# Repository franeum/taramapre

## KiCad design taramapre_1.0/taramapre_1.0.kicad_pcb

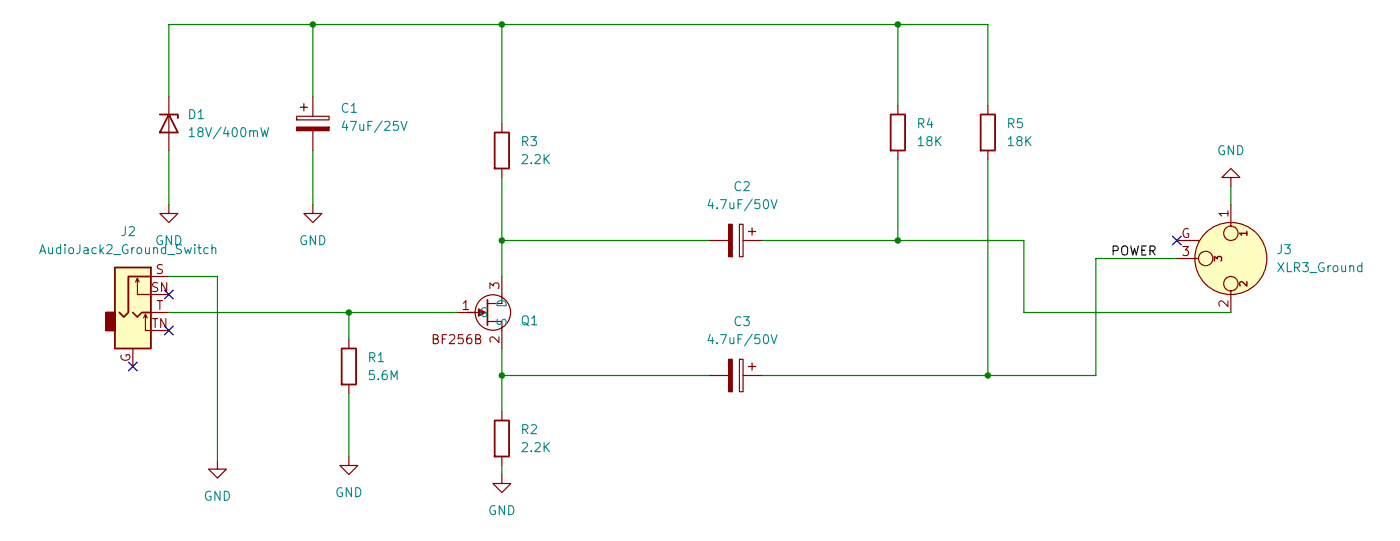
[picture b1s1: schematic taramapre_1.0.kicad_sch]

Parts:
C1: 47uF/25V; CP_Radial_D5.0mm_P2.00mm
C2, C3: 4.7uF/50V; CP_Radial_D4.0mm_P2.00mm
D1: 18V/400mW; D_DO-41_SOD81_P2.54mm_Vertical_KathodeUp
J2: AudioJack2_Ground_Switch; Jack_6.35mm_Neutrik_NMJ4HFD2_Horizontal
J3: XLR3_Ground; Jack_XLR_Neutrik_NC3MAAH_Horizontal
Q1: TO-92L_Inline
R1: 5.6M; R_Axial_DIN0207_L6.3mm_D2.5mm_P7.62mm_Horizontal
R2, R3: 2.2K; R_Axial_DIN0207_L6.3mm_D2.5mm_P7.62mm_Horizontal
R4, R5: 18K; R_Axial_DIN0207_L6.3mm_D2.5mm_P7.62mm_Horizontal

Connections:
/POWER: C3.1, J3.3, R5.2
GND: C1.2, D1.2 (A), J2.S, J3.1, R1.2, R2.2
unnamed: C2.1, J3.2, R4.2
unnamed: C1.1, D1.1 (K), R3.1, R4.1, R5.1
unnamed: C2.2, Q1.3 (D), R3.2
unnamed: J2.T, Q1.1 (G), R1.1
unnamed: C3.2, Q1.2 (S), R2.1

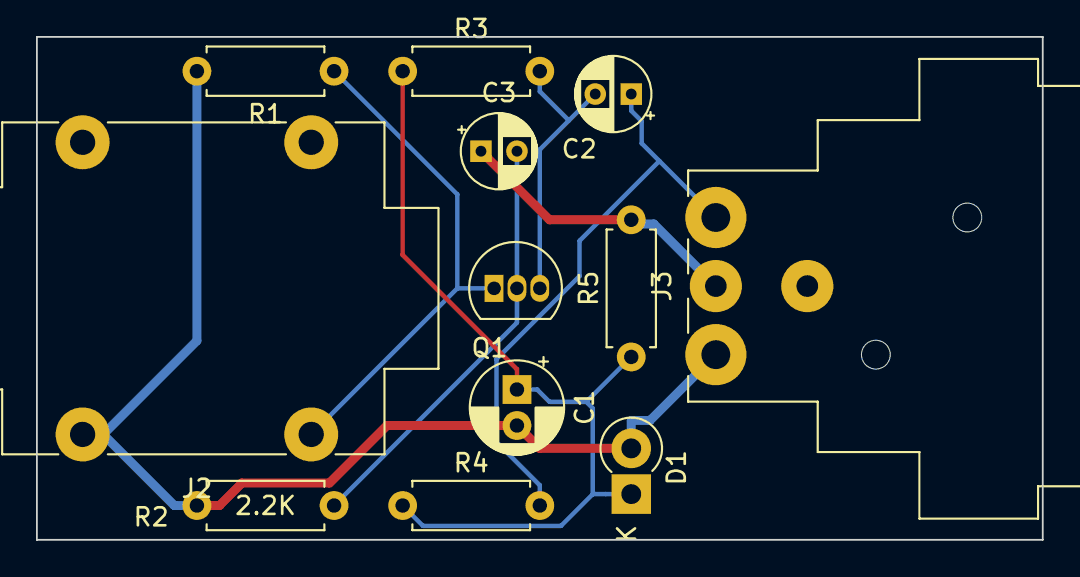
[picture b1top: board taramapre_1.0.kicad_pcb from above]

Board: 2 copper layers, 55.9 x 27.9 mm, 12 parts (0 on the bottom side), 7 nets.

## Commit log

2024-01-29 ADD: whole 0.o project
2024-02-09 ADD: v1.0 (add jack female)
2024-02-09 deleted
